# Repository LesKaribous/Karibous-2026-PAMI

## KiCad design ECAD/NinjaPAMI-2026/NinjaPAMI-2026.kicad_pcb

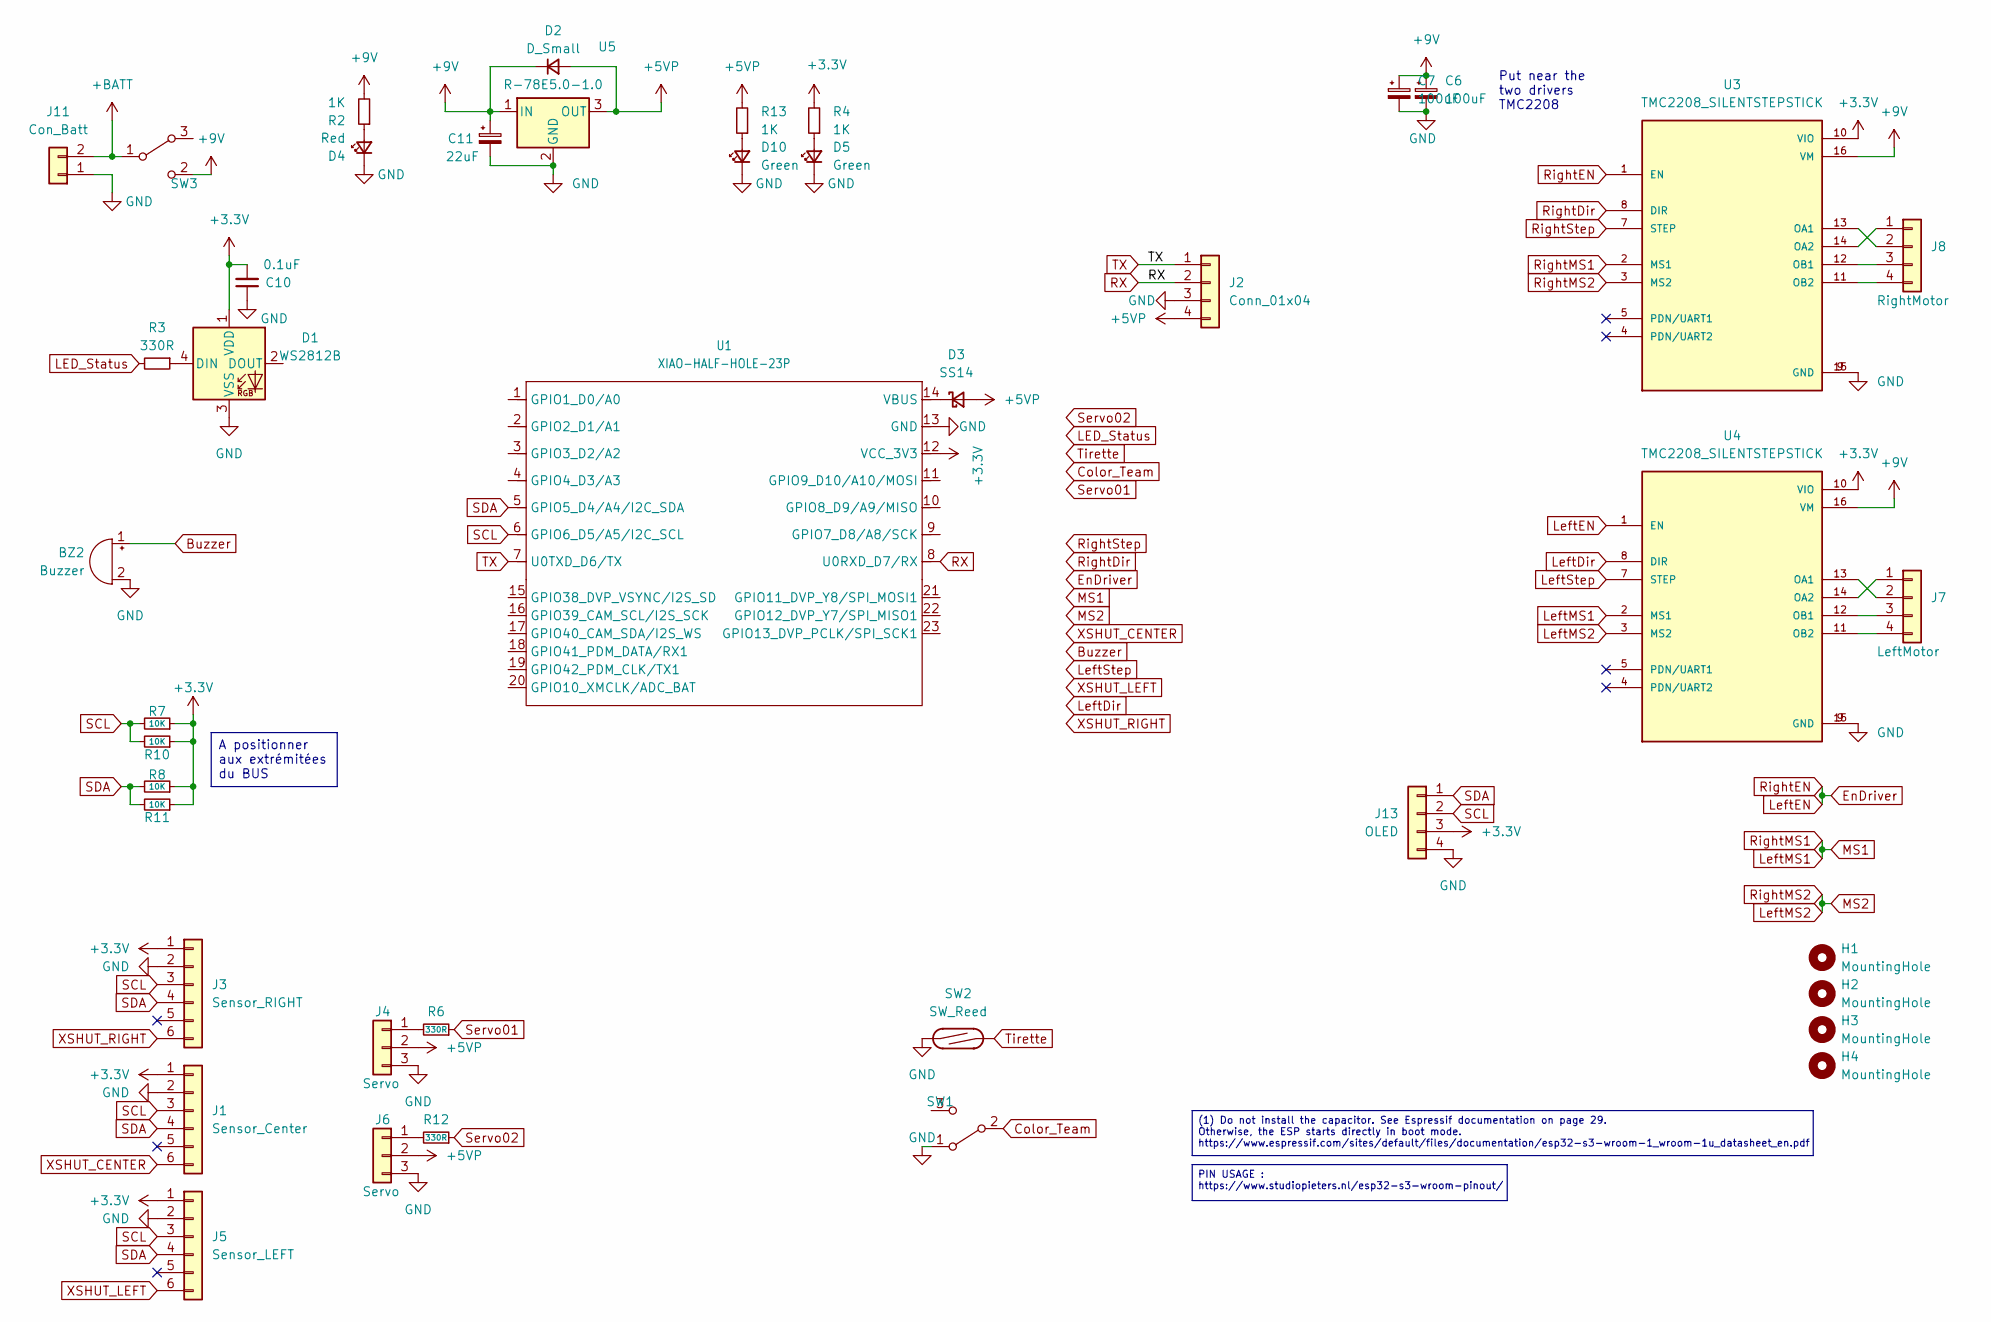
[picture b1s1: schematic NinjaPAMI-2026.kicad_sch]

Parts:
BZ2: Buzzer; Buzzer_12x9.5RM7.6
C6, C7: 100uF; CP_Radial_D8.0mm_P3.50mm
C10: 0.1uF; C_1206_3216Metric
C11: 22uF; CP_Elec_5x5.4
D1: WS2812B; LED_WS2812B_PLCC4_5.0x5.0mm_P3.2mm
D2: D_Small; D_SMA_Handsoldering
D3: SS14; D_SMA_Handsoldering
D4: Red; LED_1206_3216Metric
D5, D10: Green; LED_1206_3216Metric
H1, H2, H3, H4: MountingHole; MountingHole_3.2mm_M3
J1: Sensor_Center; VL53 Bottom Entry Version
J2: Conn_01x04; Molex_KK-254_AE-6410-04A_1x04_P2.54mm_Vertical
J3: Sensor_RIGHT; VL53 Bottom Entry Version
J4, J6: Servo; PinHeader_1x03_P2.54mm_Vertical
J5: Sensor_LEFT; VL53 Bottom Entry Version
J7: LeftMotor; PinHeader_1x04_P2.54mm_Vertical
J8: RightMotor; PinHeader_1x04_P2.54mm_Vertical
J11: Con_Batt; Molex_KK-254_AE-6410-02A_1x02_P2.54mm_Vertical
J13: OLED; PinSocket_1x04_P2.54mm_Vertical
R2, R4, R13: 1K; R_1206_3216Metric_Pad1.30x1.75mm_HandSolder
R3, R6, R12: 330R; R_1206_3216Metric_Pad1.30x1.75mm_HandSolder
R7, R8, R10, R11: 10K; R_1206_3216Metric_Pad1.30x1.75mm_HandSolder
SW1: SW_SPDT; SK-12D10 1P2T
SW2: SW_Reed; SW_SPST_REED_CT05-XXXX-G1
SW3: SW_SPDT; UB16SKW03N-C
U1: XIAO-HALF-HOLE-23P; MOUDLE23P-SMD-2.54-21X17.8MM.kicad_mod.kicad_sym
U3, U4: TMC2208_SILENTSTEPSTICK; Step-Stick Driver Bottom Entry Version
U5: R-78E5.0-1.0; Converter_DCDC_RECOM_R-78E-0.5_THT

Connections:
+3.3V: C10.2, D1.1 (VDD), J1.1, J3.1, J5.1, J13.3, R4.2, R7.1, R8.1, R10.1, R11.1, U1.12 (VCC_3V3), U3.10 (VIO), U4.10 (VIO)
+5VP: D2.2 (A), D3.2 (A), J2.4, J4.2, J6.2, R13.2, U5.3 (OUT)
+9V: C6.1, C7.1, C11.1, D2.1 (K), R2.2, SW3.2 (C), U3.16 (VM), U4.16 (VM), U5.1 (IN)
+BATT: J11.2, SW3.1 (B)
Buzzer: BZ2.1 (+)
Color_Team: SW1.2 (B)
EnDriver: U3.1 (EN), U4.1 (EN)
GND: BZ2.2 (-), C6.2, C7.2, C10.1, C11.2, D1.3 (VSS), D4.1 (K), D5.1 (K), D10.1 (K), J1.2, J2.3, J3.2, J4.3, J5.2, J6.3, J11.1, J13.4, SW1.1 (A), SW2.1, U1.13 (GND), U3.9 (GND), U3.15 (GND), U4.9 (GND), U4.15 (GND), U5.2 (GND)
LED_Status: R3.2
LeftDir: U4.8 (DIR)
LeftMS1: U3.2 (MS1), U4.2 (MS1)
LeftMS2: U3.3 (MS2), U4.3 (MS2)
LeftStep: U4.7 (STEP)
unnamed: D1.4 (DIN), R3.1
unnamed: D3.1 (K), U1.14 (VBUS)
unnamed: D4.2 (A), R2.1
unnamed: D5.2 (A), R4.1
unnamed: D10.2 (A), R13.1
unnamed: J4.1, R6.2
unnamed: J6.1, R12.2
unnamed: J7.1, U4.14 (OA2)
unnamed: J7.2, U4.13 (OA1)
unnamed: J7.3, U4.12 (OB1)
unnamed: J7.4, U4.11 (OB2)
unnamed: J8.1, U3.14 (OA2)
unnamed: J8.2, U3.13 (OA1)
unnamed: J8.3, U3.12 (OB1)
unnamed: J8.4, U3.11 (OB2)
RX: J2.2, U1.8 (U0RXD_D7/RX)
RightDir: U3.8 (DIR)
RightStep: U3.7 (STEP)
SCL: J1.3, J3.3, J5.3, J13.2, R7.2, R10.2, U1.6 (GPIO6_D5/A5/I2C_SCL)
SDA: J1.4, J3.4, J5.4, J13.1, R8.2, R11.2, U1.5 (GPIO5_D4/A4/I2C_SDA)
Servo01: R6.1
Servo02: R12.1
TX: J2.1, U1.7 (U0TXD_D6/TX)
Tirette: SW2.2
XSHUT_CENTER: J1.6
XSHUT_LEFT: J5.6
XSHUT_RIGHT: J3.6

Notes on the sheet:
Put near the two drivers TMC2208
PIN USAGE : https://www.studiopieters.nl/esp32-s3-wroom-pinout/
A positionner aux extrémitées du BUS
(1) Do not install the capacitor. See Espressif documentation on page 29. Otherwise, the ESP starts directly in boot mode. https://www.espressif.com/sites/default/files/documentation/esp32-s3-wroom-1_wroom-1u_datasheet_en.pdf

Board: 2 copper layers, 58 parts (8 on the bottom side), 27 nets, no tracks yet.

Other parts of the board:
kibuzzard-670C04A5, kibuzzard-670C04A5#2, kibuzzard-670C04A5#3, kibuzzard-670C04A5#4: G***; kibuzzard-670C04A5
kibuzzard-670C05E9: G***; kibuzzard-670C05E9
kibuzzard-670C07A3: G***; kibuzzard-670C07A3
kibuzzard-670C23C9: G***; kibuzzard-670C23C9
kibuzzard-670C045B: G***; kibuzzard-670C045B
kibuzzard-670C047F: G***; kibuzzard-670C047F
kibuzzard-670C060B: G***; kibuzzard-670C060B
kibuzzard-670C077D: G***; kibuzzard-670C077D
kibuzzard-670C0418: G***; kibuzzard-670C0418
kibuzzard-670C0436: G***; kibuzzard-670C0436
kibuzzard-670C0507: G***; kibuzzard-670C0507
kibuzzard-670C0614: G***; kibuzzard-670C0614
kibuzzard-670C0798: G***; kibuzzard-670C0798

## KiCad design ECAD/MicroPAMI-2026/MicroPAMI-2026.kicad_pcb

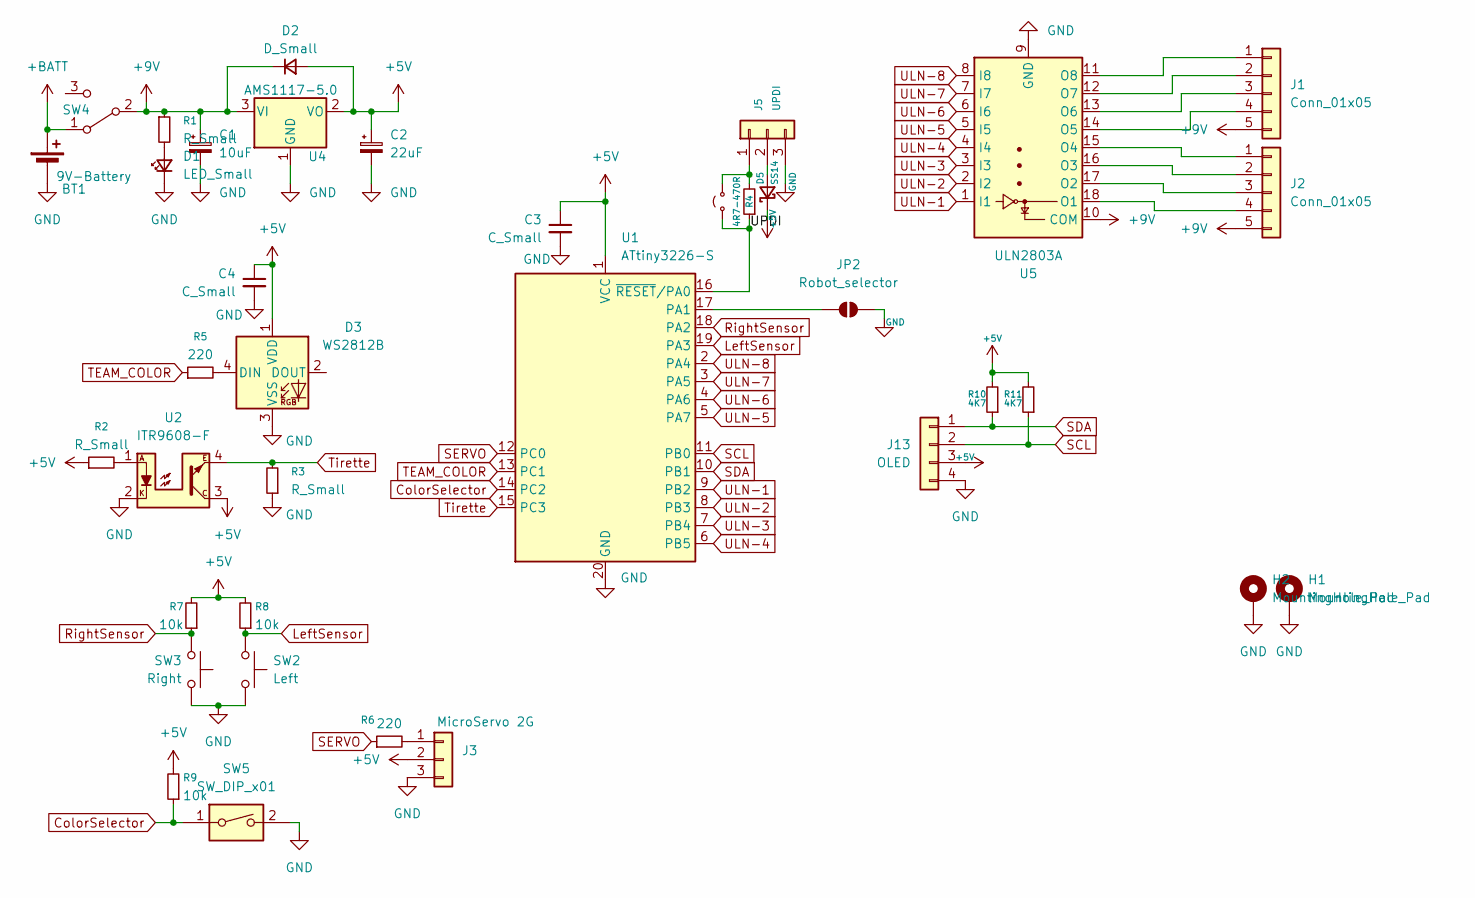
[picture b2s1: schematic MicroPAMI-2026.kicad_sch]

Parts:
BT1: 9V-Battery; 9V-PP3
C1: 10uF; CP_Elec_5x5.4
C2: 22uF; CP_EIA-3528-12_Kemet-T_Pad1.50x2.35mm_HandSolder
C3, C4: C_Small; C_1206_3216Metric_Pad1.33x1.80mm_HandSolder
D1: LED_Small; LED_1206_3216Metric_Pad1.42x1.75mm_HandSolder
D2: D_Small; D_SMA_Handsoldering
D3: WS2812B; LED_WS2812B_PLCC4_5.0x5.0mm_P3.2mm
D5: SS14; D_SMA_Handsoldering
H1, H2: MountingHole_Pad; MountingHole_3.2mm_M3_Pad_Via
J1, J2: Conn_01x05; JST_XH_B5B-XH-A_1x05_P2.50mm_Vertical
J3: MicroServo 2G; PinHeader_1x03_P2.54mm_Vertical
J5: UPDI; PinHeader_1x03_P2.54mm_Vertical
J13: OLED; PinSocket_1x04_P2.54mm_Vertical
JP1: Jumper_2_Small_Open; SolderJumper-2_P1.3mm_Open_RoundedPad1.0x1.5mm
JP2: Robot_selector; SolderJumper-2_P1.3mm_Open_RoundedPad1.0x1.5mm
R1, R2, R3: R_Small; R_1206_3216Metric_Pad1.30x1.75mm_HandSolder
R4: 4R7-470R; R_1206_3216Metric_Pad1.30x1.75mm_HandSolder
R5, R6: 220; R_1206_3216Metric_Pad1.30x1.75mm_HandSolder
R7, R8, R9: 10k; R_1206_3216Metric_Pad1.30x1.75mm_HandSolder
R10, R11: 4K7; R_1206_3216Metric_Pad1.30x1.75mm_HandSolder
SW2: Left; SW_XKB_DM1-16UP-1
SW3: Right; SW_XKB_DM1-16UP-1
SW4: SW_SPDT; SK-12D10 1P2T
SW5: SW_DIP_x01; SW_DIP_SPSTx01_Slide_9.78x4.72mm_W7.62mm_P2.54mm
U1: ATtiny3226-S; SOIC-20W_7.5x12.8mm_P1.27mm
U2: ITR9608-F; Everlight_ITR9608-F
U4: AMS1117-5.0; SOT-223-3_TabPin2
U5: ULN2803A; SOIC-18W_7.5x11.6mm_P1.27mm

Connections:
+5V: C2.1, C3.1, C4.1, D2.2 (A), D3.1 (VDD), D5.1 (K), J3.2, J13.3, R2.1, R7.2, R8.2, R9.2, R10.2, R11.2, U1.1 (VCC), U2.3, U4.2 (VO)
+9V: C1.1, D2.1 (K), J1.5, J2.5, R1.1, SW4.2 (B), U4.3 (VI), U5.10 (COM)
+BATT: BT1.1 (+), SW4.1 (A)
/UPDI: JP1.1 (A), R4.1, U1.16 (~RESET/PA0)
ColorSelector: R9.1, SW5.1, U1.14 (PC2)
GND: BT1.2 (-), C1.2, C2.2, C3.2, C4.2, D1.1 (K), D3.3 (VSS), H1.1, H2.1, J3.3, J5.3, J13.4, JP2.2 (B), R3.1, SW2.2, SW3.2, SW5.2, U1.20 (GND), U2.2, U4.1 (GND), U5.9 (GND)
LeftSensor: R8.1, SW2.1, U1.19 (PA3)
unnamed: D1.2 (A), R1.2
unnamed: D3.4 (DIN), R5.2
unnamed: D5.2 (A), J5.2
unnamed: J1.1, U5.11 (O8)
unnamed: J1.2, U5.12 (O7)
unnamed: J1.3, U5.13 (O6)
unnamed: J1.4, U5.14 (O5)
unnamed: J2.1, U5.15 (O4)
unnamed: J2.2, U5.16 (O3)
unnamed: J2.3, U5.17 (O2)
unnamed: J2.4, U5.18 (O1)
unnamed: J3.1, R6.2
unnamed: J5.1, JP1.2 (B), R4.2
unnamed: JP2.1 (A), U1.17 (PA1)
unnamed: R2.2, U2.1
RightSensor: R7.1, SW3.1, U1.18 (PA2)
SCL: J13.2, R11.1, U1.11 (PB0)
SDA: J13.1, R10.1, U1.10 (PB1)
SERVO: R6.1, U1.12 (PC0)
TEAM_COLOR: R5.1, U1.13 (PC1)
Tirette: R3.2, U1.15 (PC3), U2.4
ULN-1: U1.9 (PB2), U5.1 (I1)
ULN-2: U1.8 (PB3), U5.2 (I2)
ULN-3: U1.7 (PB4), U5.3 (I3)
ULN-4: U1.6 (PB5), U5.4 (I4)
ULN-5: U1.5 (PA7), U5.5 (I5)
ULN-6: U1.4 (PA6), U5.6 (I6)
ULN-7: U1.3 (PA5), U5.7 (I7)
ULN-8: U1.2 (PA4), U5.8 (I8)

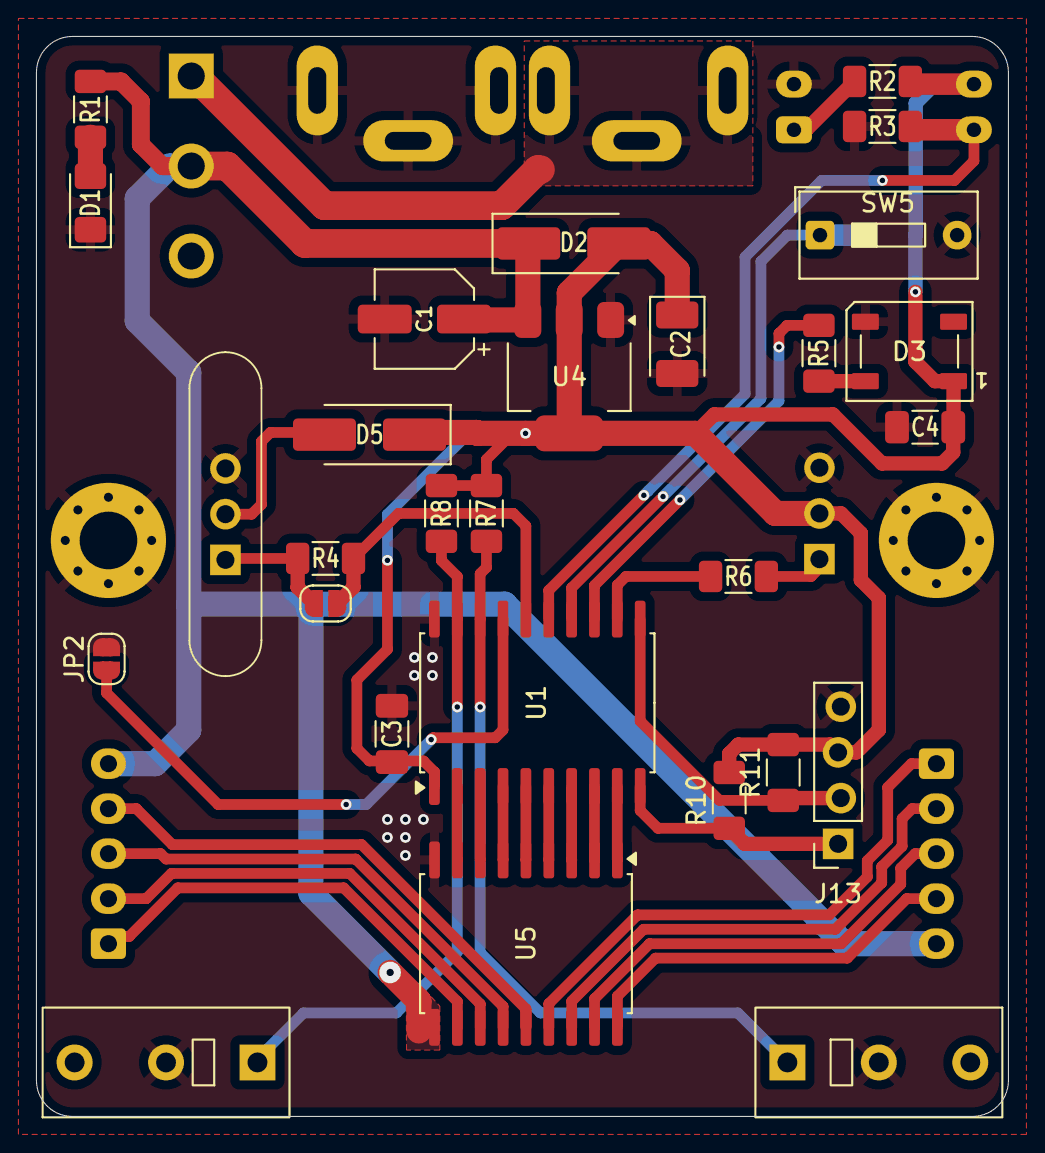
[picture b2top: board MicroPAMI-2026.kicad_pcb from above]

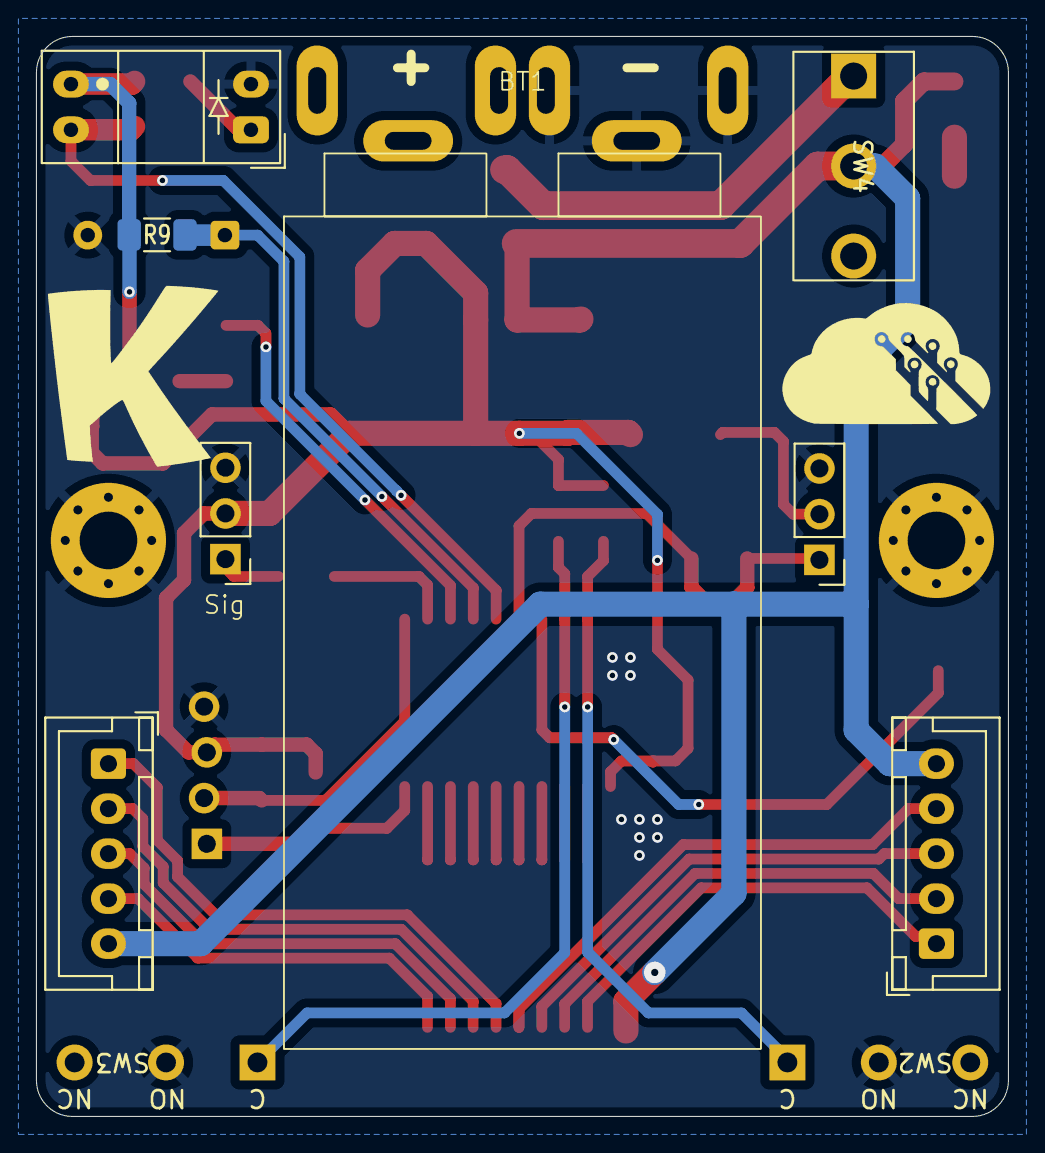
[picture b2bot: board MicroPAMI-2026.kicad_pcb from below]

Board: 2 copper layers, 54.0 x 60.0 mm, 37 parts (8 on the bottom side), 36 nets.

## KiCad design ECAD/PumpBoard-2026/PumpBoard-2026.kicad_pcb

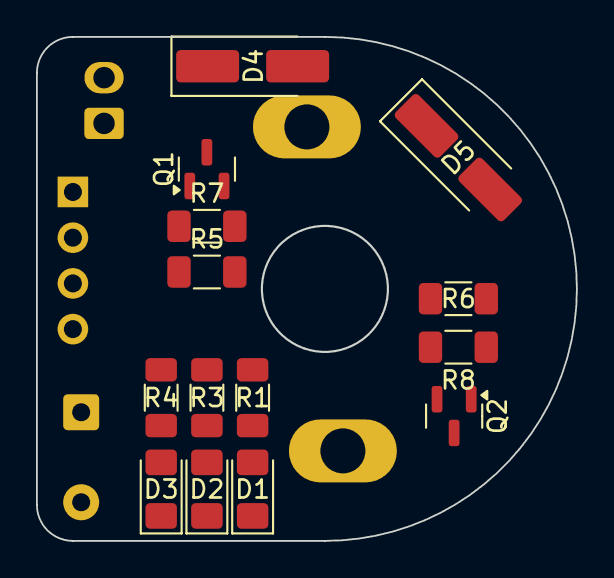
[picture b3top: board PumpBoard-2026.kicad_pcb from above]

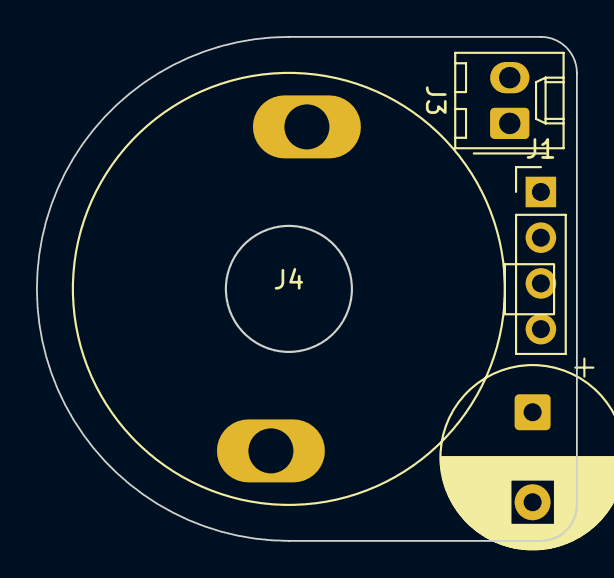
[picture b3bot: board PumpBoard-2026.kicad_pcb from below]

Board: 2 copper layers, 30.0 x 28.0 mm, 18 parts (4 on the bottom side), 11 nets, no tracks yet.

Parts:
C2: C_Polarized_Small; CP_Radial_D10.0mm_P5.00mm
D1, D2, D3: LED_Small; LED_1206_3216Metric_Pad1.42x1.75mm_HandSolder
D4, D5: D_Small; D_SMA_Handsoldering
J1: Conn_01x04; PinHeader_1x04_P2.54mm_Vertical
J3: CON_EV; Molex_KK-254_AE-6410-02A_1x02_P2.54mm_Vertical
J4: CON_PUMP; motor-pump-370
Q1, Q2: AO3400A; SOT-23
R1, R3: 1K; R_1206_3216Metric_Pad1.30x1.75mm_HandSolder
R4: 1k; R_1206_3216Metric_Pad1.30x1.75mm_HandSolder
R5, R6: 270R; R_1206_3216Metric_Pad1.30x1.75mm_HandSolder
R7, R8: 10K; R_1206_3216Metric_Pad1.30x1.75mm_HandSolder

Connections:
+5V: C2.1, D4.1 (K), D5.1 (K), J1.2, J3.2, J4.1, R1.1
GND: C2.2, D1.1 (K), D2.1 (K), D3.1 (K), J1.1, Q1.2 (S), Q2.2 (S), R7.2, R8.2
unnamed: D1.2 (A), R1.2
unnamed: D2.2 (A), R3.2
unnamed: D3.2 (A), R4.2
unnamed: D4.2 (A), J3.1, Q1.3 (D)
unnamed: D5.2 (A), J4.2, Q2.3 (D)
unnamed: Q1.1 (G), R5.1, R7.1
unnamed: Q2.1 (G), R6.2, R8.1
S_EV: J1.3, R3.1, R5.2
S_PUMP: J1.4, R4.1, R6.1

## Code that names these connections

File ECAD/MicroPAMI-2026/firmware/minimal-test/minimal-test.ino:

#include <tinyNeoPixel.h>
#include <Servo.h>
#include <Tiny4kOLED.h>

// -------------------- PINS --------------------
#define PIXEL_PIN        PIN_PC1
#define COLOR_SELECTOR   PIN_PC2
#define TIRETTE_PIN      PIN_PC3
#define SERVO_PIN        PIN_PC0

#define SENSOR_RIGHT     PIN_PA2
#define SENSOR_LEFT      PIN_PA3

// Moteur droit : PB2 PB3 PB4 PB5
#define R_IN1 PIN_PB2
#define R_IN2 PIN_PB3
#define R_IN3 PIN_PB4
#define R_IN4 PIN_PB5

// Moteur gauche : PA7 PA6 PA5 PA4
#define L_IN1 PIN_PA7
#define L_IN2 PIN_PA6
#define L_IN3 PIN_PA5
#define L_IN4 PIN_PA4

// -------------------- NEOPIXEL --------------------
#define PIXEL_COUNT 1

tinyNeoPixel pixel(
  PIXEL_COUNT,
  PIXEL_PIN,
  NEO_GRB + NEO_KHZ800
);

// -------------------- SERVO --------------------
Servo servo;

bool servoDir = false;
unsigned long lastServoUpdate = 0;
const unsigned long servoPeriod = 300; // ms

// -------------------- STEPPERS (28BYJ-48) --------------------
// Demi-pas (8 états) pour 28BYJ-48
const uint8_t halfStep[8][4] = {
  {1,0,0,0},
  {1,1,0,0},
  {0,1,0,0},
  {0,1,1,0},
  {0,0,1,0},
  {0,0,1,1},
  {0,0,0,1},
  {1,0,0,1}
};

int idxR = 0;
int idxL = 0;

void setCoilsRight(uint8_t a, uint8_t b, uint8_t c, uint8_t d) {
  digitalWrite(R_IN1, a);
  digitalWrite(R_IN2, b);
  digitalWrite(R_IN3, c);
  digitalWrite(R_IN4, d);
}

void setCoilsLeft(uint8_t a, uint8_t b, uint8_t c, uint8_t d) {
  digitalWrite(L_IN1, a);
  digitalWrite(L_IN2, b);
  digitalWrite(L_IN3, c);
  digitalWrite(L_IN4, d);
}

void stepRight(int dir) {
  idxR = (idxR + dir) & 7;
  setCoilsRight(halfStep[idxR][0], halfStep[idxR][1], halfStep[idxR][2], halfStep[idxR][3]);
}

void stepLeft(int dir) {
  idxL = (idxL + dir) & 7;
  setCoilsLeft(halfStep[idxL][0], halfStep[idxL][1], halfStep[idxL][2], halfStep[idxL][3]);
}

void releaseMotors() {
  setCoilsRight(0,0,0,0);
  setCoilsLeft(0,0,0,0);
}

// -------------------- SEQUENCE MOTEURS --------------------
// États : pause -> avant -> pause -> arrière -> pause -> rotation -> pause -> release -> pause -> boucle
enum MotorState {
  MS_IDLE = 0,
  MS_FWD,
  MS_PAUSE1,
  MS_BWD,
  MS_PAUSE2,
  MS_TURN,
  MS_PAUSE3,
  MS_RELEASE,
  MS_PAUSE4
};

MotorState motorState = MS_IDLE;

const uint16_t STEPS_PER_PHASE = 2000;     // ajuste si tu veux (512 = test court)
const uint16_t PAUSE_MS        = 300;

const uint16_t stepIntervalUs  = 1000;    // vitesse: 2000-5000 us typique (plus petit = plus rapide)

uint16_t stepsRemaining = 0;
unsigned long lastStepUs = 0;
unsigned long stateStartMs = 0;

void startMotorSequence() {
  motorState = MS_FWD;
  stepsRemaining = STEPS_PER_PHASE;
  lastStepUs = micros();
}

void stopMotorSequence() {
  motorState = MS_IDLE;
  releaseMotors();
}

void motorTick() {
  // Si en pause, gérer les transitions par millis()
  unsigned long nowMs = millis();
  unsigned long nowUs = micros();

  switch (motorState) {
    case MS_IDLE:
      // rien
      break;

    case MS_FWD:
      if ((unsigned long)(nowUs - lastStepUs) >= stepIntervalUs) {
        lastStepUs = nowUs;
        stepRight(+1);
        stepLeft(+1);
        if (--stepsRemaining == 0) {
          motorState = MS_PAUSE1;
          stateStartMs = nowMs;
        }
      }
      break;

    case MS_PAUSE1:
      if (nowMs - stateStartMs >= PAUSE_MS) {
        motorState = MS_BWD;
        stepsRemaining = STEPS_PER_PHASE;
      }
      break;

    case MS_BWD:
      if ((unsigned long)(nowUs - lastStepUs) >= stepIntervalUs) {
        lastStepUs = nowUs;
        stepRight(-1);
        stepLeft(-1);
        if (--stepsRemaining == 0) {
          motorState = MS_PAUSE2;
          stateStartMs = nowMs;
        }
      }
      break;

    case MS_PAUSE2:
      if (nowMs - stateStartMs >= PAUSE_MS) {
        motorState = MS_TURN;
        stepsRemaining = STEPS_PER_PHASE;
      }
      break;

    case MS_TURN:
      if ((unsigned long)(nowUs - lastStepUs) >= stepIntervalUs) {
        lastStepUs = nowUs;
        // rotation sur place : droite avant, gauche arrière
        stepRight(+1);
        stepLeft(-1);
        if (--stepsRemaining == 0) {
          motorState = MS_PAUSE3;
          stateStartMs = nowMs;
        }
      }
      break;

    case MS_PAUSE3:
      if (nowMs - stateStartMs >= PAUSE_MS) {
        motorState = MS_RELEASE;
      }
      break;

    case MS_RELEASE:
      releaseMotors();
      motorState = MS_PAUSE4;
      stateStartMs = nowMs;
      break;

    case MS_PAUSE4:
      if (nowMs - stateStartMs >= 1000) {
        // boucle tant que tirette LOW
        motorState = MS_FWD;
        stepsRemaining = STEPS_PER_PHASE;
      }
      break;
  }
}

// -------------------- SETUP / LOOP --------------------
void setup() {
  pinMode(COLOR_SELECTOR, INPUT_PULLUP);
  pinMode(TIRETTE_PIN, INPUT_PULLUP);

  pinMode(SENSOR_RIGHT, INPUT_PULLUP);
  pinMode(SENSOR_LEFT, INPUT_PULLUP);

  pixel.begin();
  pixel.show();

    // Initialisation I2C (Wire interne, pins PB0/PB1 automatiques)
  oled.begin();

  // Configuration écran 96x16
  oled.clear();
  oled.on();
  oled.setFont(FONT6X8);
  oled.setRotation(2);

  // Position curseur (x, ligne)
  oled.setCursor(0, 0);
  oled.print("OLED 96x16");

  oled.setCursor(0, 1);
  oled.print("I2C OK");

  servo.attach(SERVO_PIN);
  servo.write(90);

  pinMode(R_IN1, OUTPUT); pinMode(R_IN2, OUTPUT); pinMode(R_IN3, OUTPUT); pinMode(R_IN4, OUTPUT);
  pinMode(L_IN1, OUTPUT); pinMode(L_IN2, OUTPUT); pinMode(L_IN3, OUTPUT); pinMode(L_IN4, OUTPUT);
  releaseMotors();
}

void loop() {
  // Lecture tirette
  bool tiretteLow = (digitalRead(TIRETTE_PIN) == LOW);

  // Démarrage/arrêt de la séquence moteurs selon tirette
  static bool motorRunning = false;
  if (tiretteLow && !motorRunning) {
    motorRunning = true;
    startMotorSequence();
  } else if (!tiretteLow && motorRunning) {
    motorRunning = false;
    stopMotorSequence();
  }

  // Tick moteurs (non bloquant)
  if (motorRunning) {
    motorTick();
  }

  // Lecture capteurs (LOW = detecte)
  bool rightLow = (digitalRead(SENSOR_RIGHT) == LOW);
  bool leftLow  = (digitalRead(SENSOR_LEFT)  == LOW);
  bool obstacle = rightLow || leftLow;

  // ----- NeoPixel (priorité capteurs) -----
  if (obstacle) {
    pixel.setPixelColor(0, pixel.Color(0, 255, 0));          // Vert
  } else if (tiretteLow) {
    pixel.setPixelColor(0, pixel.Color(255, 0, 0));          // Rouge
  } else {
    if (digitalRead(COLOR_SELECTOR) == HIGH) {
      pixel.setPixelColor(0, pixel.Color(0, 0, 255));        // Bleu
    } else {
      pixel.setPixelColor(0, pixel.Color(255, 255, 0));      // Jaune
    }
  }
  pixel.show();

  // ----- Servo -----
  if (tiretteLow) {
    if (millis() - lastServoUpdate >= servoPeriod) {
      lastServoUpdate = millis();
      servoDir = !servoDir;
      servo.write(servoDir ? 45 : 90);
    }
  } else {
    servo.write(90);
  }
}

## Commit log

2025-11-29 Add squirrel design
2025-11-30 update designs
2025-12-07 proto ninja
2025-12-07 live 246
2025-12-10 new attiny mini version
2025-12-10 new mini pump pcb
2025-12-10 change capacitor size
2025-12-10 Update PCB: add resistors, change net assignments
    Added R3 and R8 SMD resistors to the PCB layout and updated net assignments for several signals, including connections for Tirette, LeftSensor, and others. Replaced unconnected net labels with specif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
2025-12-30 Update battery position and change component orientation
2025-12-30 Board routing
2025-12-30 Create PCB part and wheels
2025-12-31 update BAU - add oled
2025-12-31 Add Gh-S37D Servo STEP file and update MicroPami.FCStd
2025-12-31 add a robot selector jumper
2026-01-01 add I2C resistor
2026-01-07 add pogo for programming
2026-01-13 update to production POC
2026-01-13 New ninja pami 2026
2026-01-15 change dimensions
2026-01-19 change uC value
2026-01-19 solve real pcb integration
2026-01-21 pio adaptation - include accelstepper
2026-01-24 new pcb export
2026-01-24 new wheel design
2026-01-24 modify body for pull start
2026-01-24 Update Main-body.3mf 3D model file
2026-01-24 PAMI ninja PCB update
2026-01-24 add mini eyes capabilities
2026-01-24 clean code - Add eyes - separate functions
2026-01-24 add stop on opponent
2026-01-25 new front panel
2026-01-25 new front panel for micro PAMI
2026-01-25 transfer "PAMI Ninja" to dedicated repo
2026-01-25 add "tirette"
2026-03-04 Import firmware from 2025
2026-03-24 strategy 2026
2026-04-10 new tirette
2026-04-15 import firmware micro PAMI
2026-04-15 add design
2026-04-15 update strategy for 2026
2026-04-16 new design
2026-04-19 Belgium 2026
